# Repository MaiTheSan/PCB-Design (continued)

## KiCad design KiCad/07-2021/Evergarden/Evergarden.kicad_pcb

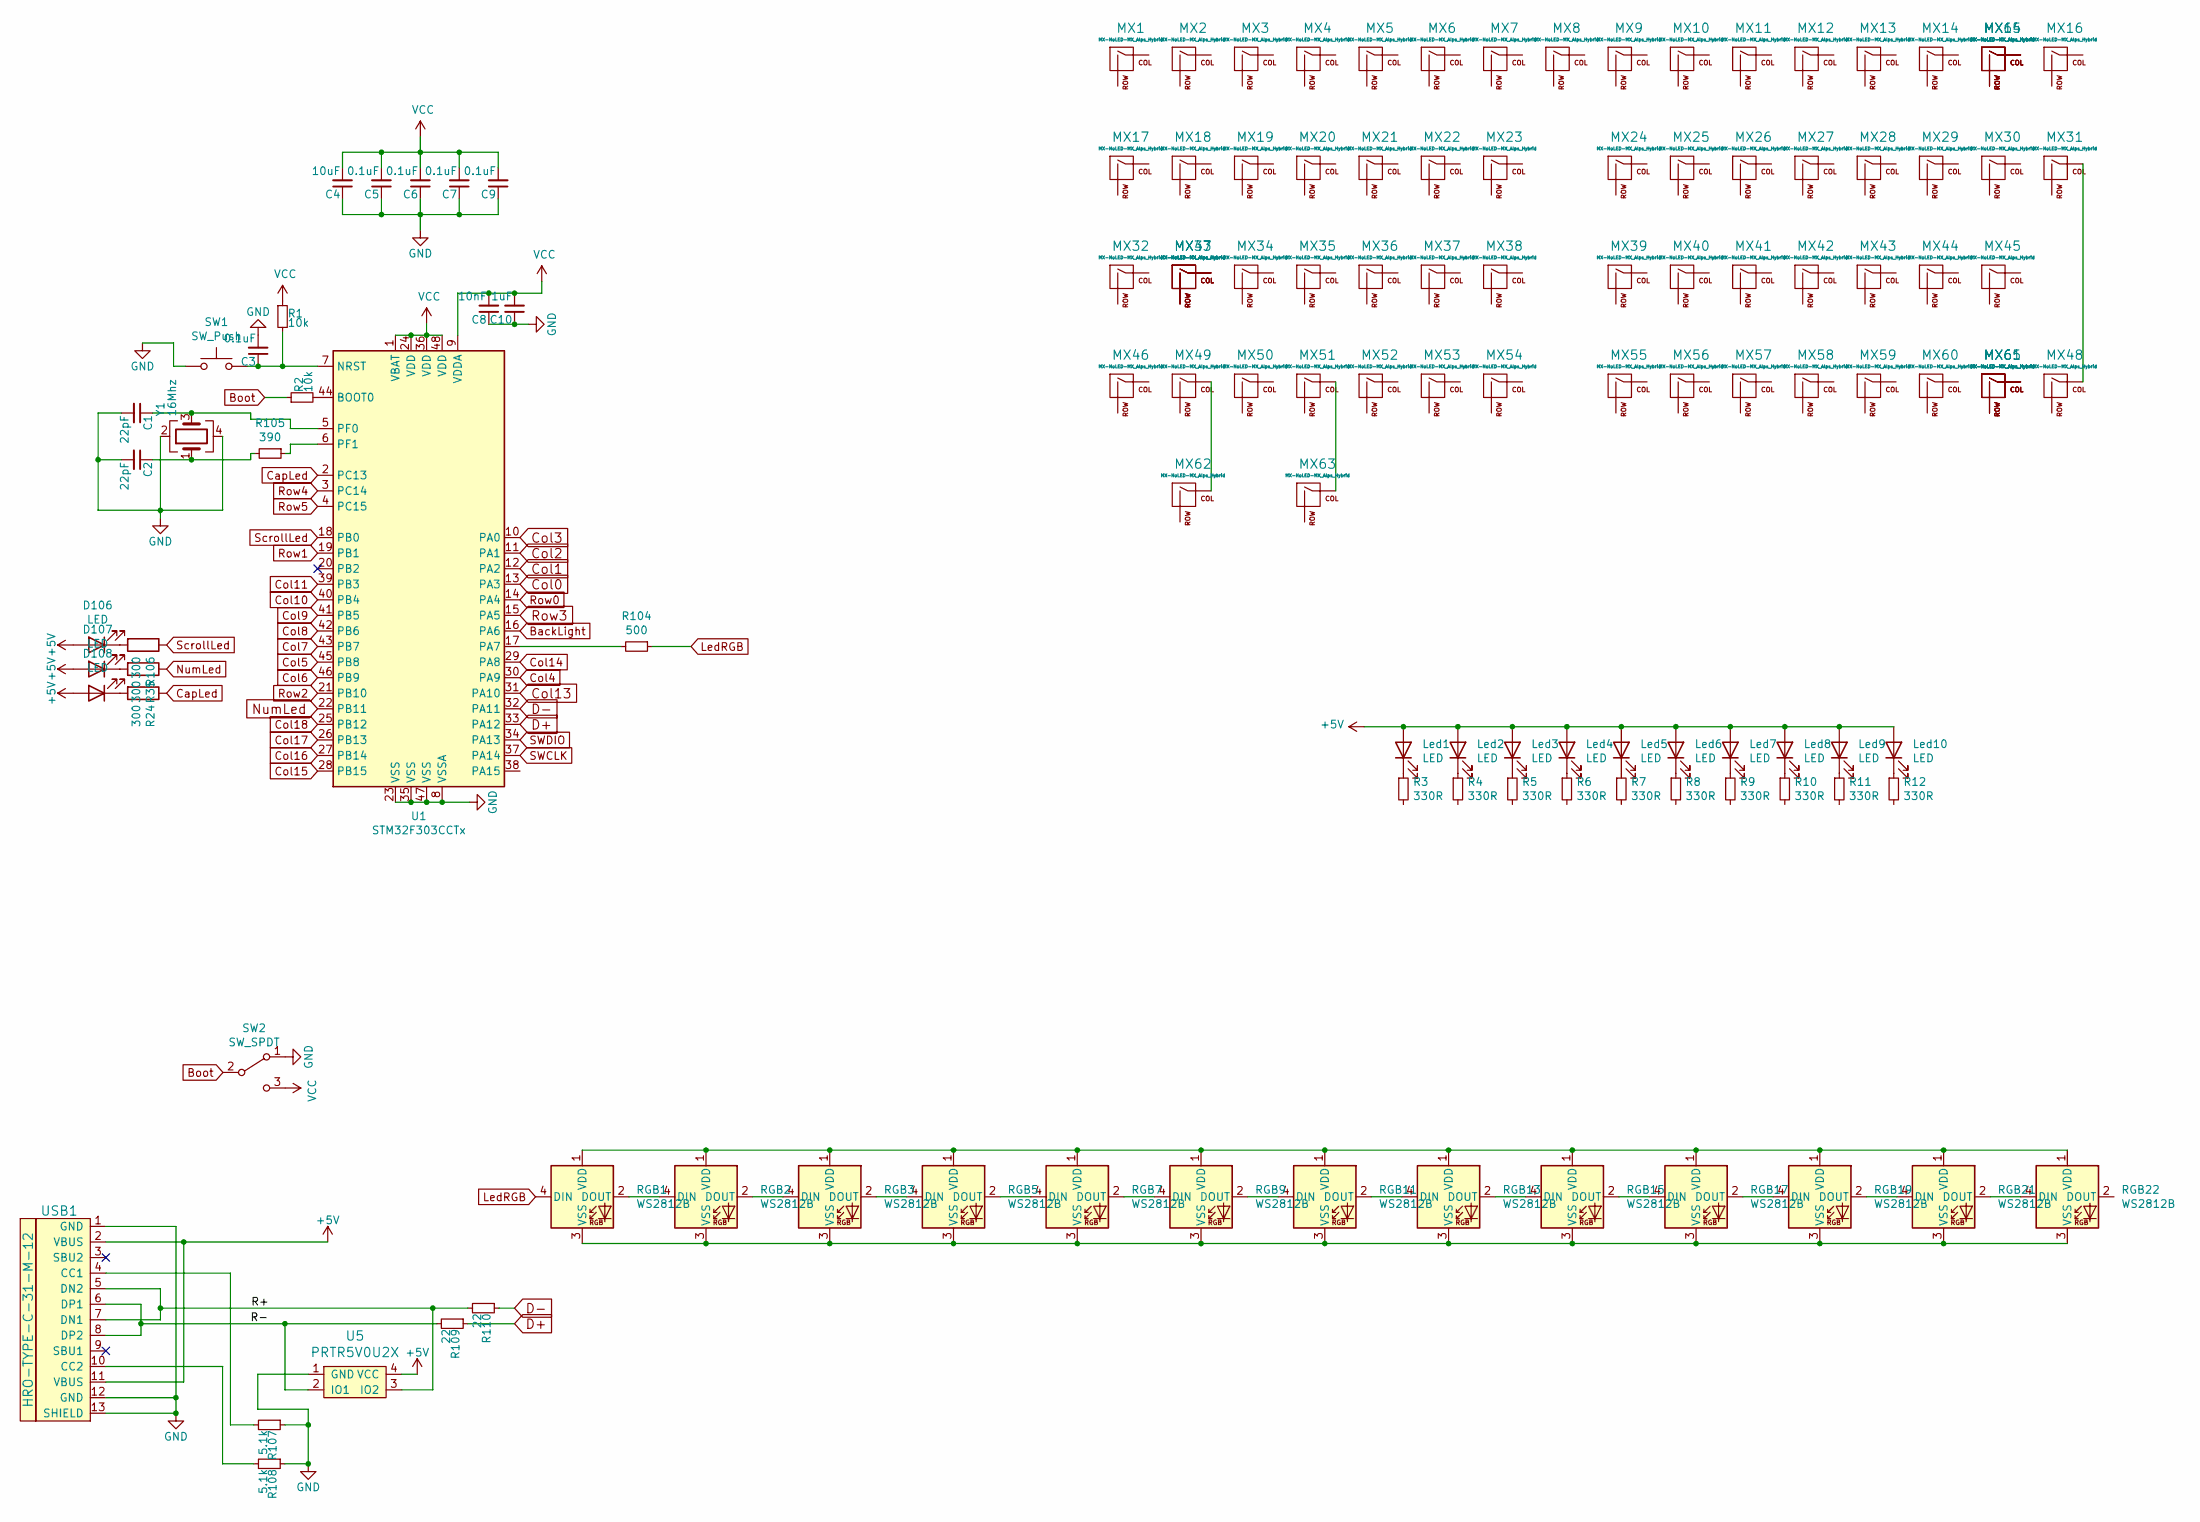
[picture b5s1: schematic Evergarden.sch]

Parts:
C1, C2: 22pF; C_0603
C3, C5, C6, C7, C9: 0.1uF; C_0603
C4: 10uF; C_0603
C8: 10nF; C_0603
C10: 1uF; C_0603
D106, D107, D108: LED; MXOnly-LEDONLY-MID
Led1, Led2, Led3, Led4, Led5, Led6, Led7, Led8, Led9, Led10: LED; MXOnly-LEDONLY
MX1, MX2, MX3, MX4, MX5, MX6, MX7, MX8, MX9, MX10, MX11, MX12, MX13, MX14, MX15, MX16, MX17, MX19, MX20, MX21, MX22, MX23, MX24, MX25, MX26, MX27, MX28, MX29, MX30, MX32, MX34, MX35, MX36, MX37, MX38, MX39, MX40, MX41, MX42, MX43, MX44, MX46, MX48, MX50, MX51, MX52, MX53, MX54, MX55, MX56, MX57, MX58, MX59, MX60, MX62, MX63: MX-NoLED-MX_Alps_Hybrid; MXOnly-1U-NoLED
MX18, MX31: MX-NoLED-MX_Alps_Hybrid; MXOnly-1.5U-NoLED
MX33, MX65: MX-NoLED-MX_Alps_Hybrid; MXOnly-1.75U-NoLED
MX45: MX-NoLED-MX_Alps_Hybrid; MXOnly-2.25U-ReversedStabilizers-NoLED
MX47: MX-NoLED-MX_Alps_Hybrid; MXOnly-1.25U-NoLED
MX49, MX61: MX-NoLED-MX_Alps_Hybrid; MXOnly-2.25U-NoLED
MX64: MX-NoLED-MX_Alps_Hybrid; MXOnly-2U-NoLED
R1, R2: 10k; R_0805
R3, R4, R5, R6, R7, R8, R9, R10, R11, R12: 330R; C_0603
R24, R35, R106: 300; R_0805
R104: 500; R_0805
R105: 390; R_0805
R107, R108: 5.1k; R_0805
R109, R110: 22; R_0805
RGB1, RGB2, RGB3, RGB5, RGB7, RGB9, RGB11, RGB13, RGB15, RGB17, RGB19, RGB21, RGB22: WS2812B; LED_WS2812B_PLCC4_5.0x5.0mm_P3.2mm
SW1: SW_Push; SKQG-1155865
SW2: SW_SPDT; SW_SPDT_PCM12
U1: STM32F303CCTx; LQFP-48_7x7mm_P0.5mm
U5: PRTR5V0U2X; SOT143B
USB1: HRO-TYPE-C-31-M-12; HRO-TYPE-C-31-M-12-Assembly
Y1: 16Mhz; Crystal_SMD_3225-4Pin_3.2x2.5mm

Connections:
+5V: D106.2 (A), D107.2 (A), D108.2 (A), Led1.2 (A), Led2.2 (A), Led3.2 (A), Led4.2 (A), Led5.2 (A), Led6.2 (A), Led7.2 (A), Led8.2 (A), Led9.2 (A), Led10.2 (A), U5.4 (VCC), USB1.2 (VBUS), USB1.11 (VBUS)
/R+: R110.2, U5.3 (IO2), USB1.5 (DN2), USB1.7 (DN1)
/R-: R109.2, U5.2 (IO1), USB1.6 (DP1), USB1.8 (DP2)
BackLight: U1.16 (PA6)
Boot: R2.1, SW2.2 (B)
CapLed: R24.1, U1.2 (PC13)
Col0: U1.13 (PA3)
Col1: U1.12 (PA2)
Col2: U1.11 (PA1)
Col3: U1.10 (PA0)
Col4: U1.30 (PA9)
Col5: U1.45 (PB8)
Col6: U1.46 (PB9)
Col7: U1.43 (PB7)
Col8: U1.42 (PB6)
Col9: U1.41 (PB5)
Col10: U1.40 (PB4)
Col11: U1.39 (PB3)
Col13: U1.31 (PA10)
Col14: U1.29 (PA8)
Col15: U1.28 (PB15)
Col16: U1.27 (PB14)
Col17: U1.26 (PB13)
Col18: U1.25 (PB12)
D+: R109.1, U1.33 (PA12)
D-: R110.1, U1.32 (PA11)
GND: C1.2, C2.2, C3.2, C4.1, C5.1, C6.1, C7.1, C8.1, C9.1, C10.1, R107.1, R108.1, SW1.1, SW2.1 (A), U1.8 (VSSA), U1.23 (VSS), U1.35 (VSS), U1.47 (VSS), U5.1 (GND), USB1.1 (GND), USB1.12 (GND), USB1.13 (SHIELD), Y1.2, Y1.4
LedRGB: R104.1, RGB1.4 (DIN)
unnamed: C1.1, U1.5 (PF0), Y1.3
unnamed: C2.1, R105.2, Y1.1
unnamed: C3.1, R1.2, SW1.2, U1.7 (NRST)
unnamed: D106.1 (K), R106.2
unnamed: D107.1 (K), R35.2
unnamed: D108.1 (K), R24.2
unnamed: Led1.1 (K), R3.1
unnamed: Led2.1 (K), R4.1
unnamed: Led3.1 (K), R5.1
unnamed: Led4.1 (K), R6.1
unnamed: Led5.1 (K), R7.1
unnamed: Led6.1 (K), R8.1
unnamed: Led7.1 (K), R9.1
unnamed: Led8.1 (K), R10.1
unnamed: Led9.1 (K), R11.1
unnamed: Led10.1 (K), R12.1
unnamed: MX15.1 (COL), MX64.1 (COL)
unnamed: MX15.2 (ROW), MX64.2 (ROW)
unnamed: MX31.1 (COL), MX48.1 (COL)
unnamed: MX33.1 (COL), MX47.1 (COL)
unnamed: MX33.2 (ROW), MX47.2 (ROW)
unnamed: MX49.1 (COL), MX62.1 (COL)
unnamed: MX51.1 (COL), MX63.1 (COL)
unnamed: MX61.1 (COL), MX65.1 (COL)
unnamed: MX61.2 (ROW), MX65.2 (ROW)
unnamed: R2.2, U1.44 (BOOT0)
unnamed: R104.2, U1.17 (PA7)
unnamed: R105.1, U1.6 (PF1)
unnamed: R107.2, USB1.4 (CC1)
unnamed: R108.2, USB1.10 (CC2)
unnamed: RGB1.1 (VDD), RGB2.1 (VDD), RGB3.1 (VDD), RGB5.1 (VDD), RGB7.1 (VDD), RGB9.1 (VDD), RGB11.1 (VDD), RGB13.1 (VDD), RGB15.1 (VDD), RGB17.1 (VDD), RGB19.1 (VDD), RGB21.1 (VDD), RGB22.1 (VDD)
unnamed: RGB1.2 (DOUT), RGB2.4 (DIN)
unnamed: RGB1.3 (VSS), RGB2.3 (VSS), RGB3.3 (VSS), RGB5.3 (VSS), RGB7.3 (VSS), RGB9.3 (VSS), RGB11.3 (VSS), RGB13.3 (VSS), RGB15.3 (VSS), RGB17.3 (VSS), RGB19.3 (VSS), RGB21.3 (VSS), RGB22.3 (VSS)
unnamed: RGB2.2 (DOUT), RGB3.4 (DIN)
unnamed: RGB3.2 (DOUT), RGB5.4 (DIN)
unnamed: RGB5.2 (DOUT), RGB7.4 (DIN)
unnamed: RGB7.2 (DOUT), RGB9.4 (DIN)
unnamed: RGB11.2 (DOUT), RGB13.4 (DIN)
unnamed: RGB9.2 (DOUT), RGB11.4 (DIN)
unnamed: RGB13.2 (DOUT), RGB15.4 (DIN)
unnamed: RGB15.2 (DOUT), RGB17.4 (DIN)
unnamed: RGB17.2 (DOUT), RGB19.4 (DIN)
unnamed: RGB19.2 (DOUT), RGB21.4 (DIN)
unnamed: RGB21.2 (DOUT), RGB22.4 (DIN)
NumLed: R35.1, U1.22 (PB11)
Row0: U1.14 (PA4)
Row1: U1.19 (PB1)
Row2: U1.21 (PB10)
Row3: U1.15 (PA5)
Row4: U1.3 (PC14)
Row5: U1.4 (PC15)
SWCLK: U1.37 (PA14)
SWDIO: U1.34 (PA13)
ScrollLed: R106.1, U1.18 (PB0)
VCC: C4.2, C5.2, C6.2, C7.2, C8.2, C9.2, C10.2, R1.1, SW2.3 (C), U1.1 (VBAT), U1.9 (VDDA), U1.24 (VDD), U1.36 (VDD), U1.48 (VDD)

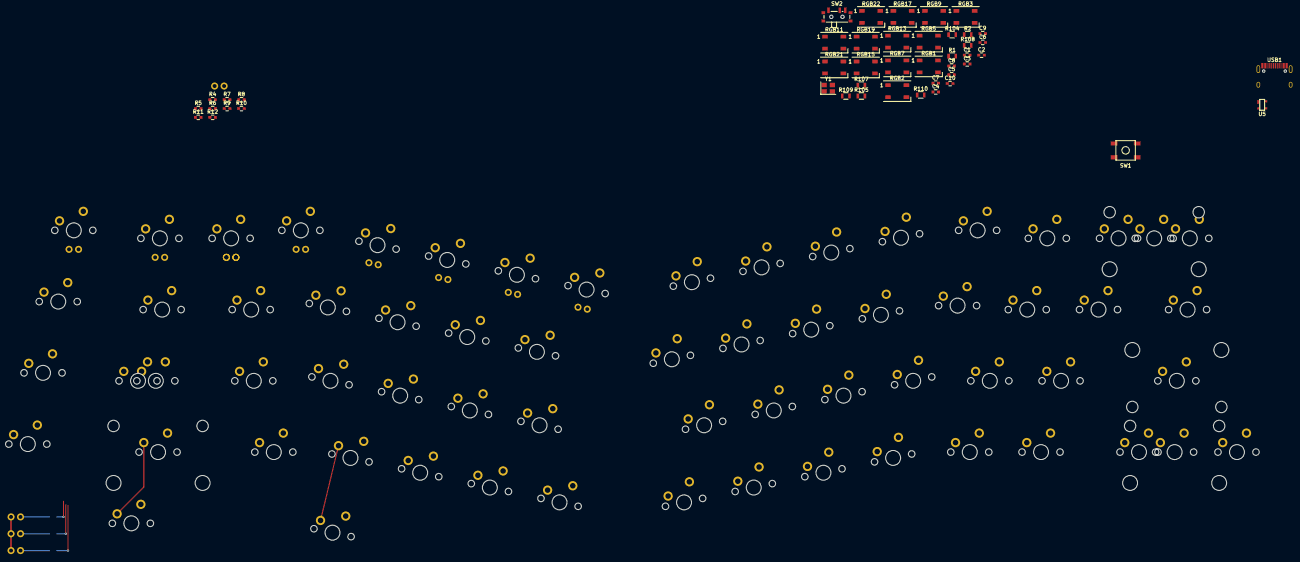
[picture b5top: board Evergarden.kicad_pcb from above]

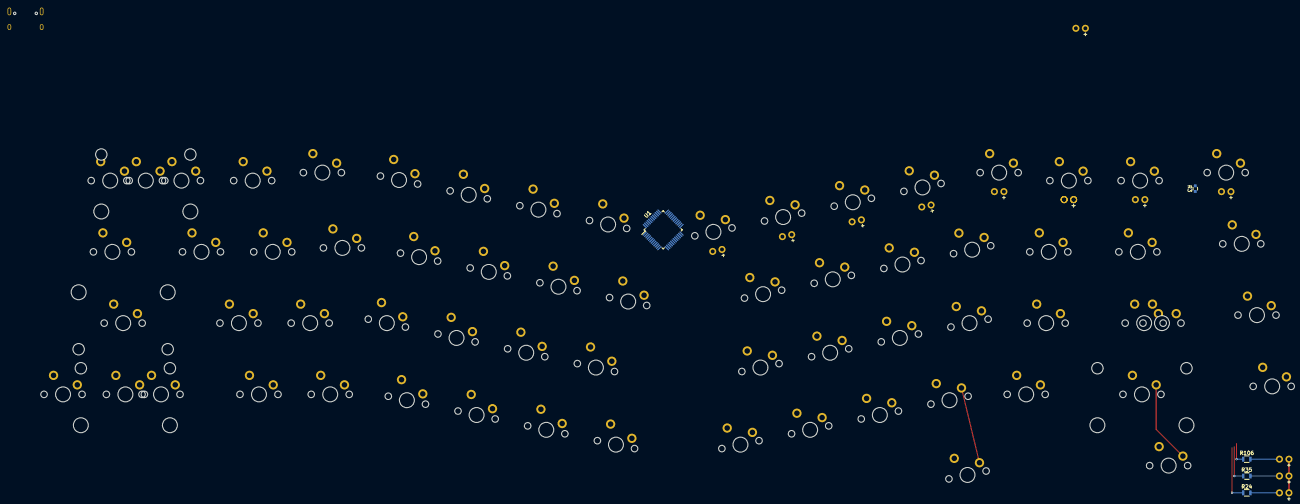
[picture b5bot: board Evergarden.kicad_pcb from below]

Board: 2 copper layers, 128 parts (5 on the bottom side), 56 nets.
